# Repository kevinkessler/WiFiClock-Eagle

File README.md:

PCB Eagle Files for WifiClock project

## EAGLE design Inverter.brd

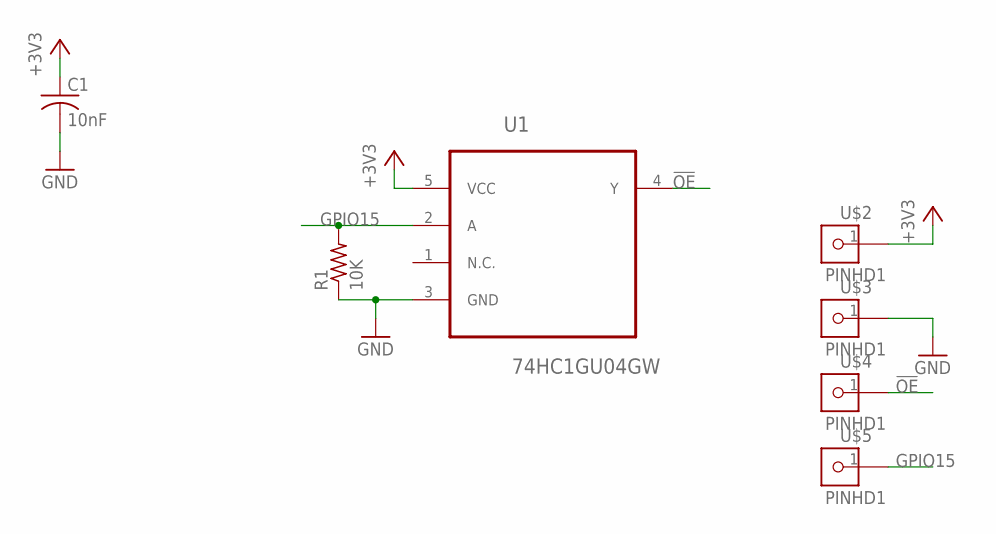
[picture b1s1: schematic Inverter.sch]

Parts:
C1: 10nF; C0805K
R1: 10K; M0805
U1: 74HC1GU04GW; SOT65P210X110-5N
U$2, U$3, U$4, U$5: PINHD1; 1X1

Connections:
!OE: U1.4 (Y), U$4.1
+3V3: C1.1, U1.5 (VCC), U$2.1
GND: C1.2, R1.1, U1.3 (GND), U$3.1
GPIO15: R1.2, U1.2 (A), U$5.1

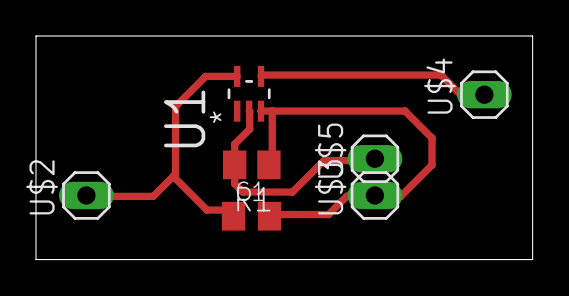
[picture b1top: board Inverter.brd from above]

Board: 2 copper layers, 27.6 x 12.4 mm, 7 parts (0 on the bottom side), 4 nets.

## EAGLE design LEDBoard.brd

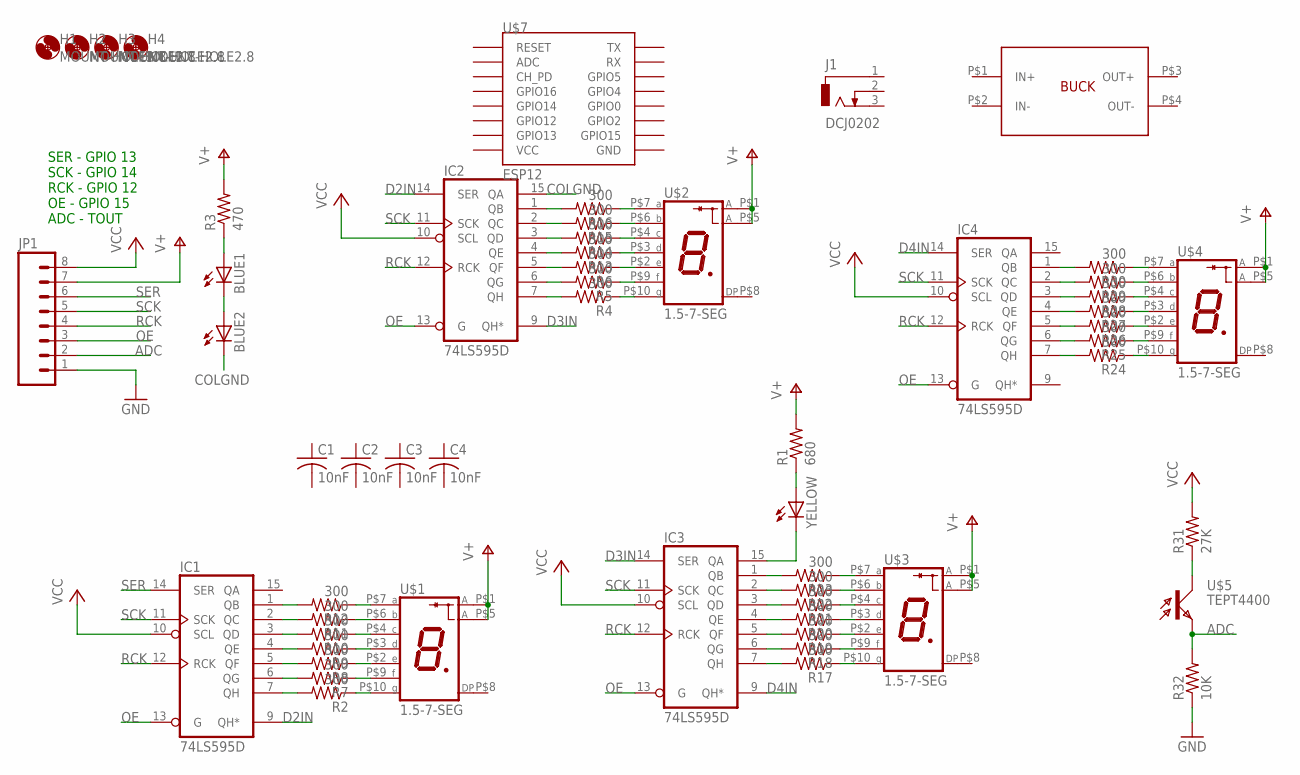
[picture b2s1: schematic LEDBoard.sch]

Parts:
BLUE1, BLUE2: LED3MM
C1, C2, C3, C4: 10nF; C0805K
H1, H2, H3, H4: MOUNT-HOLE2.8; 2,8
IC1, IC2, IC3, IC4: 74LS595D; SO16
J1: DCJ0202
JP1: M08SMD-MALE; 1X08_SMD_MALE
R1: 680; M0805
R2, R4, R5, R6, R7, R8, R9, R10, R11, R12, R13, R14, R15, R16, R17, R18, R19, R20, R21, R22, R23, R24, R25, R26, R27, R28, R29, R30: 300; M0805
R3: 470; M0805
R31: 27K; M0805
R32: 10K; M0805
U$1, U$2, U$3, U$4: 1.5-7-SEG
U$5: TEPT4400; T1
U$6: BUCK_CONV
U$7: ESP12
YELLOW: LED3MM

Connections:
ADC: JP1.2, R32.2, U$5.A (E)
COLGND: BLUE2.K (C), IC2.15 (QA)
D2IN: IC1.9 (QH*), IC2.14 (SER)
D3IN: IC2.9 (QH*), IC3.14 (SER)
D4IN: IC3.9 (QH*), IC4.14 (SER)
GND: IC1.8 (GND), IC2.8 (GND), IC3.8 (GND), IC4.8 (GND), JP1.1, R32.1
unnamed: IC1.1 (QB), R12.2
unnamed: R1.1, YELLOW.A
unnamed: BLUE1.A, R3.1
unnamed: BLUE1.K (C), BLUE2.A
unnamed: R12.1, U$1.P$7 (A)
unnamed: IC1.2 (QC), R11.2
unnamed: R11.1, U$1.P$6 (B)
unnamed: IC1.3 (QD), R10.2
unnamed: R10.1, U$1.P$4 (C)
unnamed: IC1.4 (QE), R9.2
unnamed: R9.1, U$1.P$3 (D)
unnamed: IC1.5 (QF), R8.2
unnamed: R8.1, U$1.P$2 (E)
unnamed: IC1.6 (QG), R7.2
unnamed: R7.1, U$1.P$9 (F)
unnamed: IC1.7 (QH), R2.2
unnamed: R2.1, U$1.P$10 (G)
unnamed: IC2.1 (QB), R16.2
unnamed: R16.1, U$2.P$7 (A)
unnamed: IC2.2 (QC), R15.2
unnamed: R31.1, U$5.K (C)
unnamed: R15.1, U$2.P$6 (B)
unnamed: IC2.3 (QD), R14.2
unnamed: R14.1, U$2.P$4 (C)
unnamed: IC2.4 (QE), R13.2
unnamed: R13.1, U$2.P$3 (D)
unnamed: IC2.5 (QF), R6.2
unnamed: R6.1, U$2.P$2 (E)
unnamed: IC2.6 (QG), R5.2
unnamed: R5.1, U$2.P$9 (F)
unnamed: IC2.7 (QH), R4.2
unnamed: R4.1, U$2.P$10 (G)
unnamed: IC3.1 (QB), R23.2
unnamed: R23.1, U$3.P$7 (A)
unnamed: IC3.2 (QC), R22.2
unnamed: R22.1, U$3.P$6 (B)
unnamed: IC3.3 (QD), R21.2
unnamed: R21.1, U$3.P$4 (C)
unnamed: IC3.4 (QE), R20.2
unnamed: R20.1, U$3.P$3 (D)
unnamed: IC3.5 (QF), R19.2
unnamed: R19.1, U$3.P$2 (E)
unnamed: IC3.6 (QG), R18.2
unnamed: R18.1, U$3.P$9 (F)
unnamed: IC3.7 (QH), R17.2
unnamed: R17.1, U$3.P$10 (G)
unnamed: IC4.1 (QB), R30.2
unnamed: R30.1, U$4.P$7 (A)
unnamed: IC4.2 (QC), R29.2
unnamed: R29.1, U$4.P$6 (B)
unnamed: IC4.3 (QD), R28.2
unnamed: R28.1, U$4.P$4 (C)
unnamed: IC4.4 (QE), R27.2
unnamed: R27.1, U$4.P$3 (D)
unnamed: IC4.5 (QF), R26.2
unnamed: R26.1, U$4.P$2 (E)
unnamed: IC4.6 (QG), R25.2
unnamed: R25.1, U$4.P$9 (F)
unnamed: IC4.7 (QH), R24.2
unnamed: R24.1, U$4.P$10 (G)
unnamed: IC3.15 (QA), YELLOW.K (C)
OE: IC1.13 (G), IC2.13 (G), IC3.13 (G), IC4.13 (G), JP1.3
RCK: IC1.12 (RCK), IC2.12 (RCK), IC3.12 (RCK), IC4.12 (RCK), JP1.4
SCK: IC1.11 (SCK), IC2.11 (SCK), IC3.11 (SCK), IC4.11 (SCK), JP1.5
SER: IC1.14 (SER), JP1.6
V+: JP1.7, R1.2, R3.2, U$1.P$1 (A), U$1.P$5 (A), U$2.P$1 (A), U$2.P$5 (A), U$3.P$1 (A), U$3.P$5 (A), U$4.P$1 (A), U$4.P$5 (A)
VCC: IC1.10 (SCL), IC1.16 (VCC), IC2.10 (SCL), IC2.16 (VCC), IC3.10 (SCL), IC3.16 (VCC), IC4.10 (SCL), IC4.16 (VCC), JP1.8, R31.2

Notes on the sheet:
SER - GPIO 13 SCK - GPIO 14 RCK - GPIO 12 OE - GPIO 15 ADC - TOUT

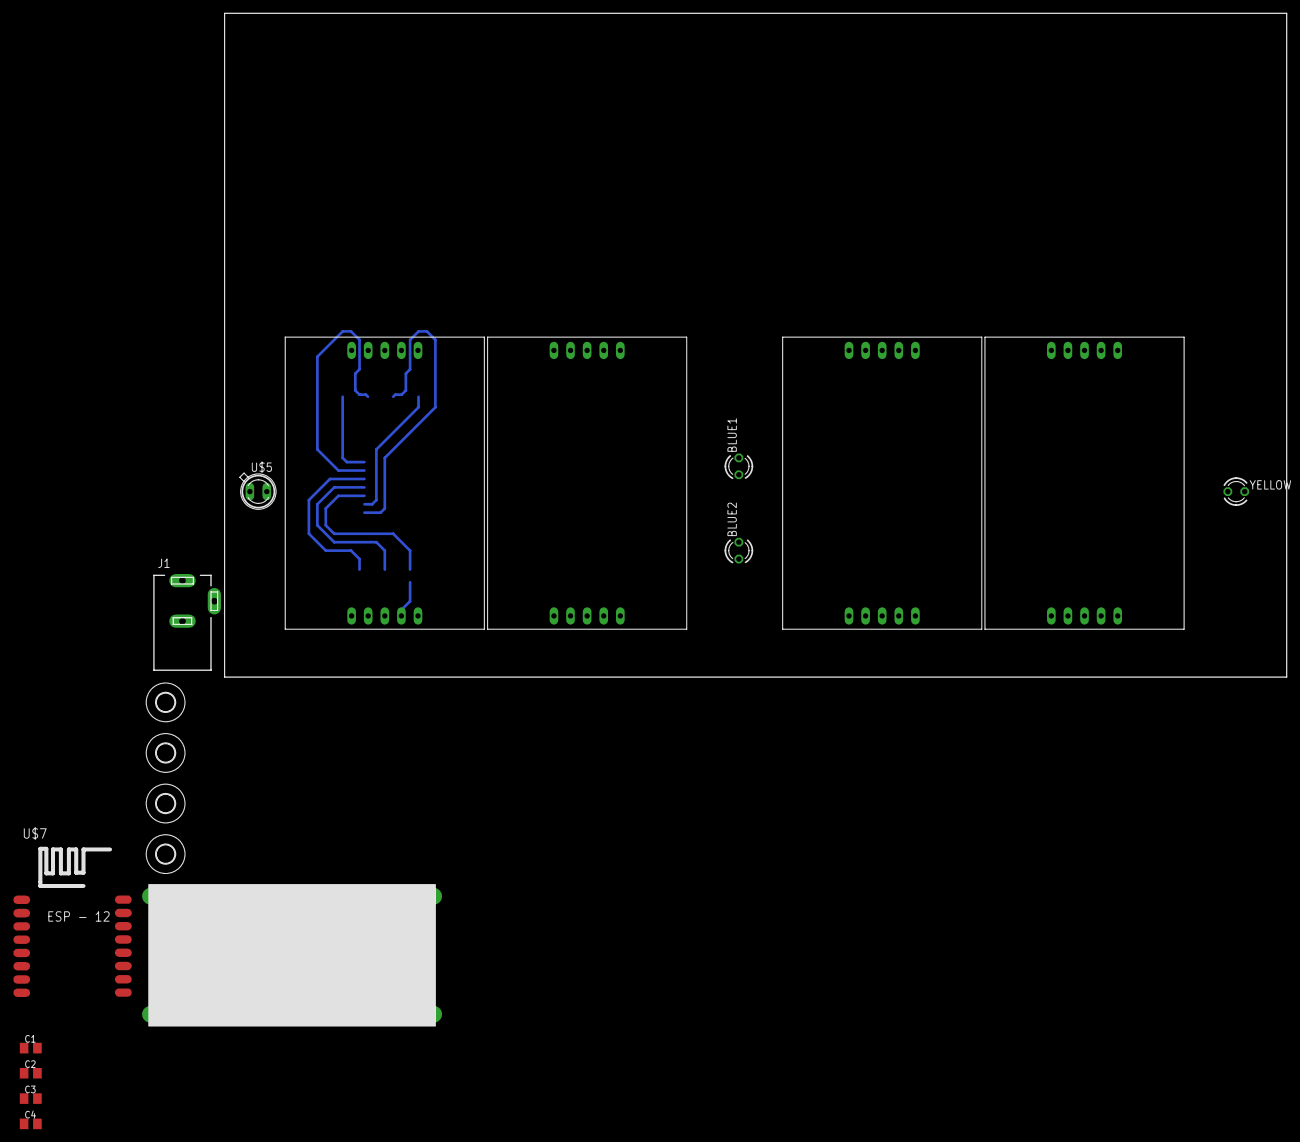
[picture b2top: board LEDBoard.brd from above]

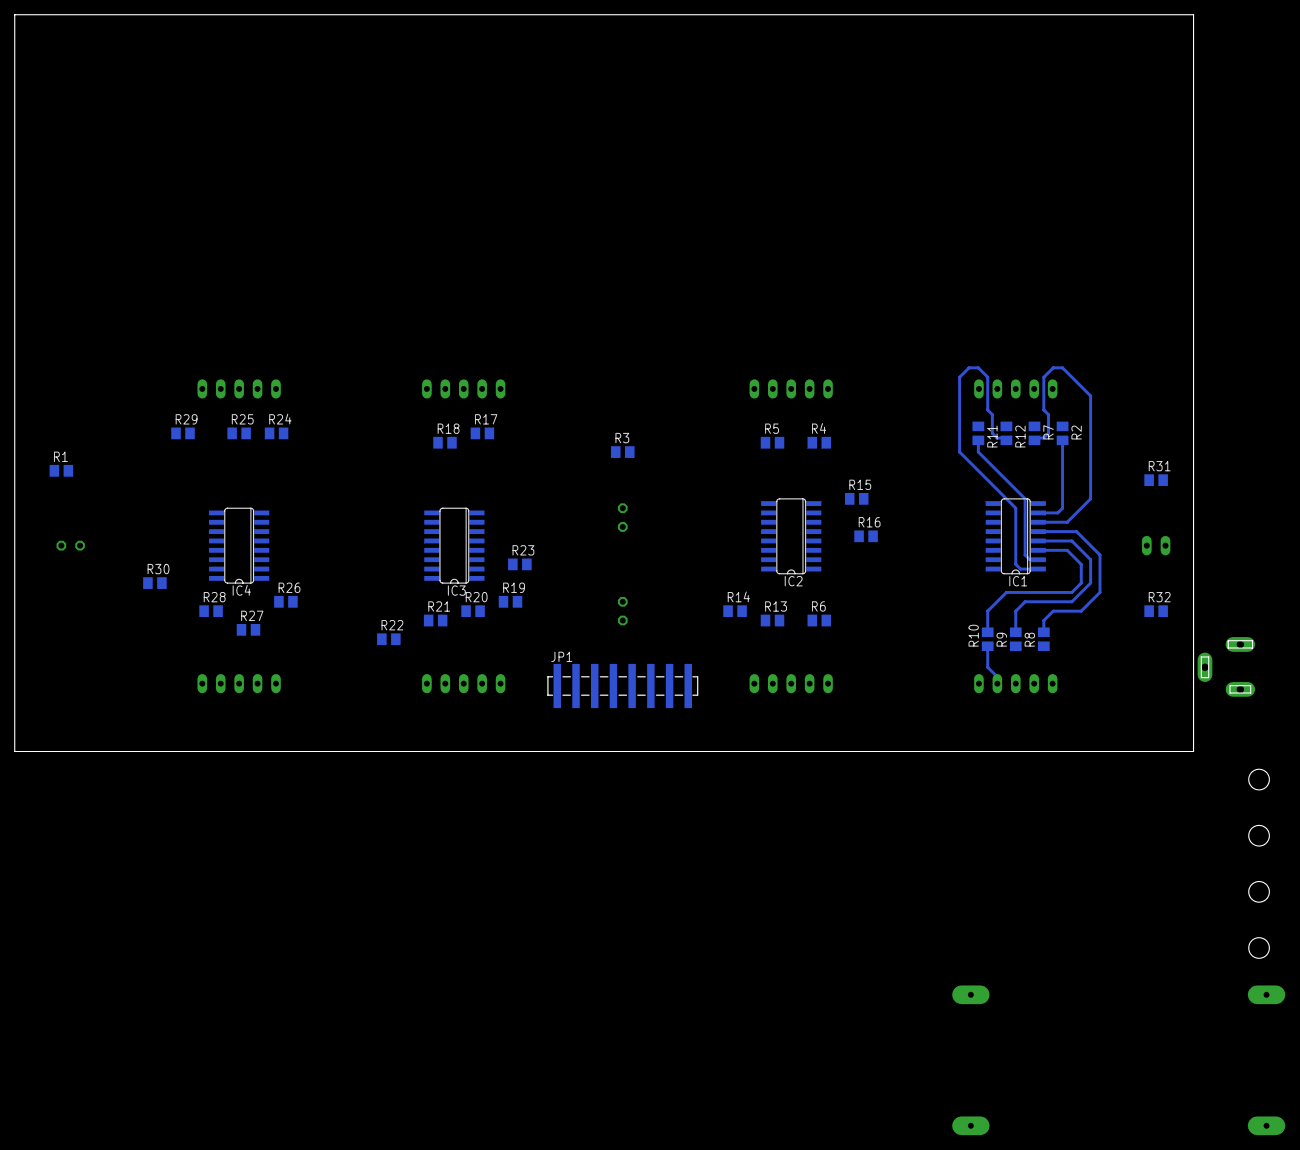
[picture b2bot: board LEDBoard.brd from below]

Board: 2 copper layers, 168.0 x 100.0 mm, 56 parts (37 on the bottom side), 73 nets.

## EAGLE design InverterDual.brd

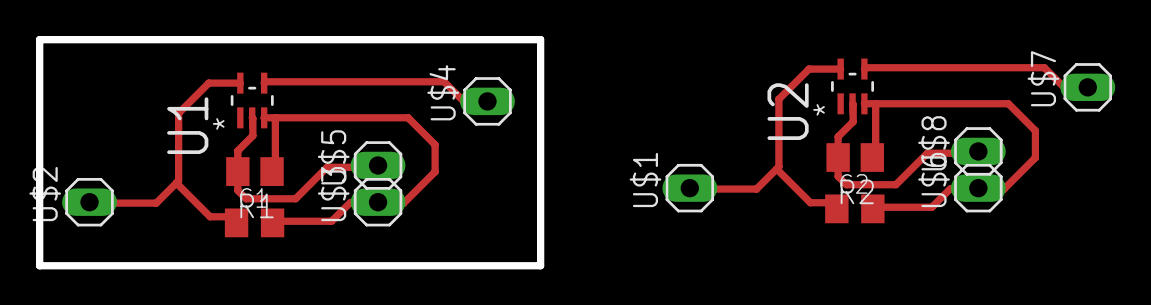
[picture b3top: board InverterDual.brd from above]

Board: 2 copper layers, 27.8 x 12.6 mm, 14 parts (0 on the bottom side), 8 nets.

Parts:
C1, C2: 10nF; C0805K
R1, R2: 10K; M0805
U1, U2: 74HC1GU04GW; SOT65P210X110-5N
U$1, U$2, U$3, U$4, U$5, U$6, U$7, U$8: PINHD1; 1X1

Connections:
!OE: U1.4, U$4.1
!OE1: U2.4, U$7.1
+3V1: C2.1, U2.5, U$1.1
+3V3: C1.1, U1.5, U$2.1
GND: C1.2, R1.1, U1.3, U$3.1
GND1: C2.2, R2.1, U2.3, U$6.1
GPIO1: R2.2, U2.2, U$8.1
GPIO15: R1.2, U1.2, U$5.1

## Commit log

2016-03-13 Create Repository

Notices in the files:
parts and their libraries:
SparkFun-Connectors: Licensing: Creative Commons ShareAlike 4.0 International - https://creativecommons.org/licenses/by-sa/4.0
